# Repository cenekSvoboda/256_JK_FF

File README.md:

# 256_JK_FF
256 JK FlipFlop practical implementation

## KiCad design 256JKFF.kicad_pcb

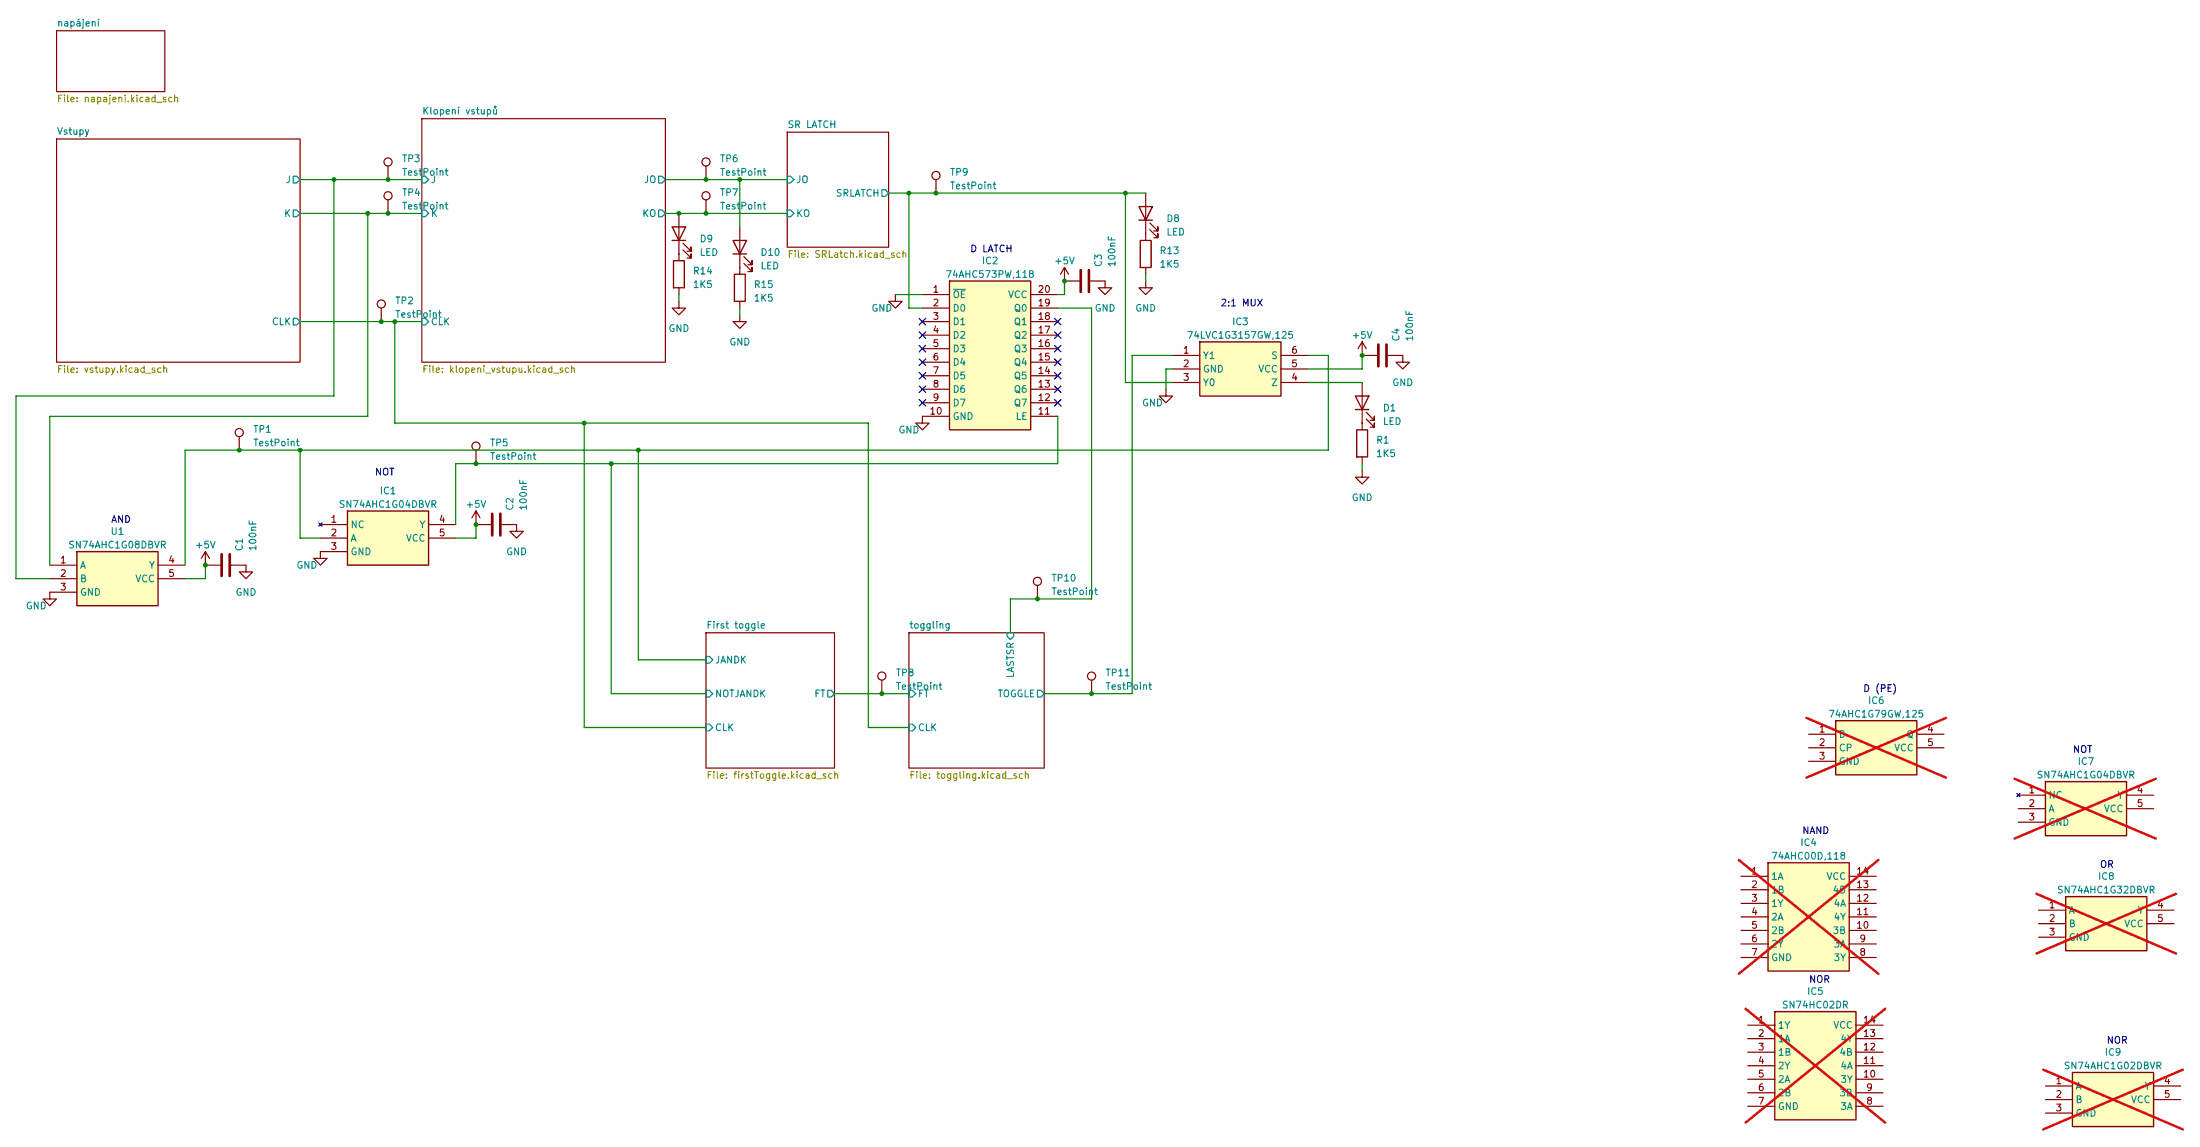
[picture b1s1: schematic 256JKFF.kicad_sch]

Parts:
C1, C2, C3, C4: 100nF; C_1206_3216Metric
D1: LED; LED_D3.0mm
D8, D9, D10: LED; LED_1206_3216Metric
IC1: SN74AHC1G04DBVR; SOT95P280X145-5N; Manufacturer_Part_Number SN74AHC1G04DBVR
IC2: 74AHC573PW,118; SOIC127P1032X265-20N; Manufacturer_Part_Number 74AHC573PW,118
IC3: 74LVC1G3157GW,125; 74LVC1G3157GW125; Manufacturer_Part_Number 74LVC1G3157GW,125
IC4: 74AHC00D,118; SOIC127P600X175-14N; Manufacturer_Part_Number 74AHC00D,118; not fitted
IC5: SN74HC02DR; SOIC127P600X175-14N; Manufacturer_Part_Number SN74HC02DR; not fitted
IC6: 74AHC1G79GW,125; SOT65P212X110-5N; Manufacturer_Part_Number 74AHC1G79GW,125; not fitted
IC7: SN74AHC1G04DBVR; SOT95P280X145-5N; Manufacturer_Part_Number SN74AHC1G04DBVR; not fitted
IC8: SN74AHC1G32DBVR; SOT95P280X145-5N; Manufacturer_Part_Number SN74AHC1G32DBVR; not fitted
IC9: SN74AHC1G02DBVR; SOT95P280X145-5N; Manufacturer_Part_Number SN74AHC1G02DBVR; not fitted
R1, R13, R14, R15: 1K5; R_1206_3216Metric
TP1, TP2, TP3, TP4, TP5, TP6, TP7, TP8, TP9, TP10, TP11: TestPoint; TestPoint_Pad_1.5x1.5mm
U1: SN74AHC1G08DBVR; SOT95P280X145-5N; Manufacturer_Part_Number SN74AHC1G08DBVR

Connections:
+5V: C1.2, C2.2, C3.2, C4.2, IC1.5 (VCC), IC2.20 (VCC), IC3.5 (VCC), U1.5 (VCC); also elsewhere on the board
/First toggle/CLK: TP2.1; also elsewhere on the board
/First toggle/FT: TP8.1; also elsewhere on the board
/First toggle/JANDK: IC1.2 (A), IC3.6 (S), TP1.1, U1.4 (Y); also elsewhere on the board
/First toggle/NOTJANDK: IC1.4 (Y), IC2.11 (LE), TP5.1; also elsewhere on the board
/Klopení vstupů/J: TP3.1, U1.2 (B); also elsewhere on the board
/Klopení vstupů/JO: D10.2 (A), TP6.1; also elsewhere on the board
/Klopení vstupů/K: TP4.1, U1.1 (A); also elsewhere on the board
/Klopení vstupů/KO: D9.2 (A), TP7.1; also elsewhere on the board
/SR LATCH/SRLATCH: D8.2 (A), IC2.2 (D0), IC3.3 (Y0), TP9.1; also elsewhere on the board
/toggling/LASTSR: IC2.19 (Q0), TP10.1; also elsewhere on the board
/toggling/TOGGLE: IC3.1 (Y1), TP11.1; also elsewhere on the board
GND: C1.1, C2.1, C3.1, C4.1, IC1.3 (GND), IC2.1 (~OE), IC2.10 (GND), IC3.2 (GND), R1.2, R13.2, R14.2, R15.2, U1.3 (GND); also elsewhere on the board
unnamed: D1.2 (A), IC3.4 (Z)
unnamed: D1.1 (K), R1.1
unnamed: D8.1 (K), R13.1
unnamed: D9.1 (K), R14.1
unnamed: D10.1 (K), R15.1

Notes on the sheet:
D (PE)
NAND
AND
NOT
2:1 MUX
NOR
D LATCH

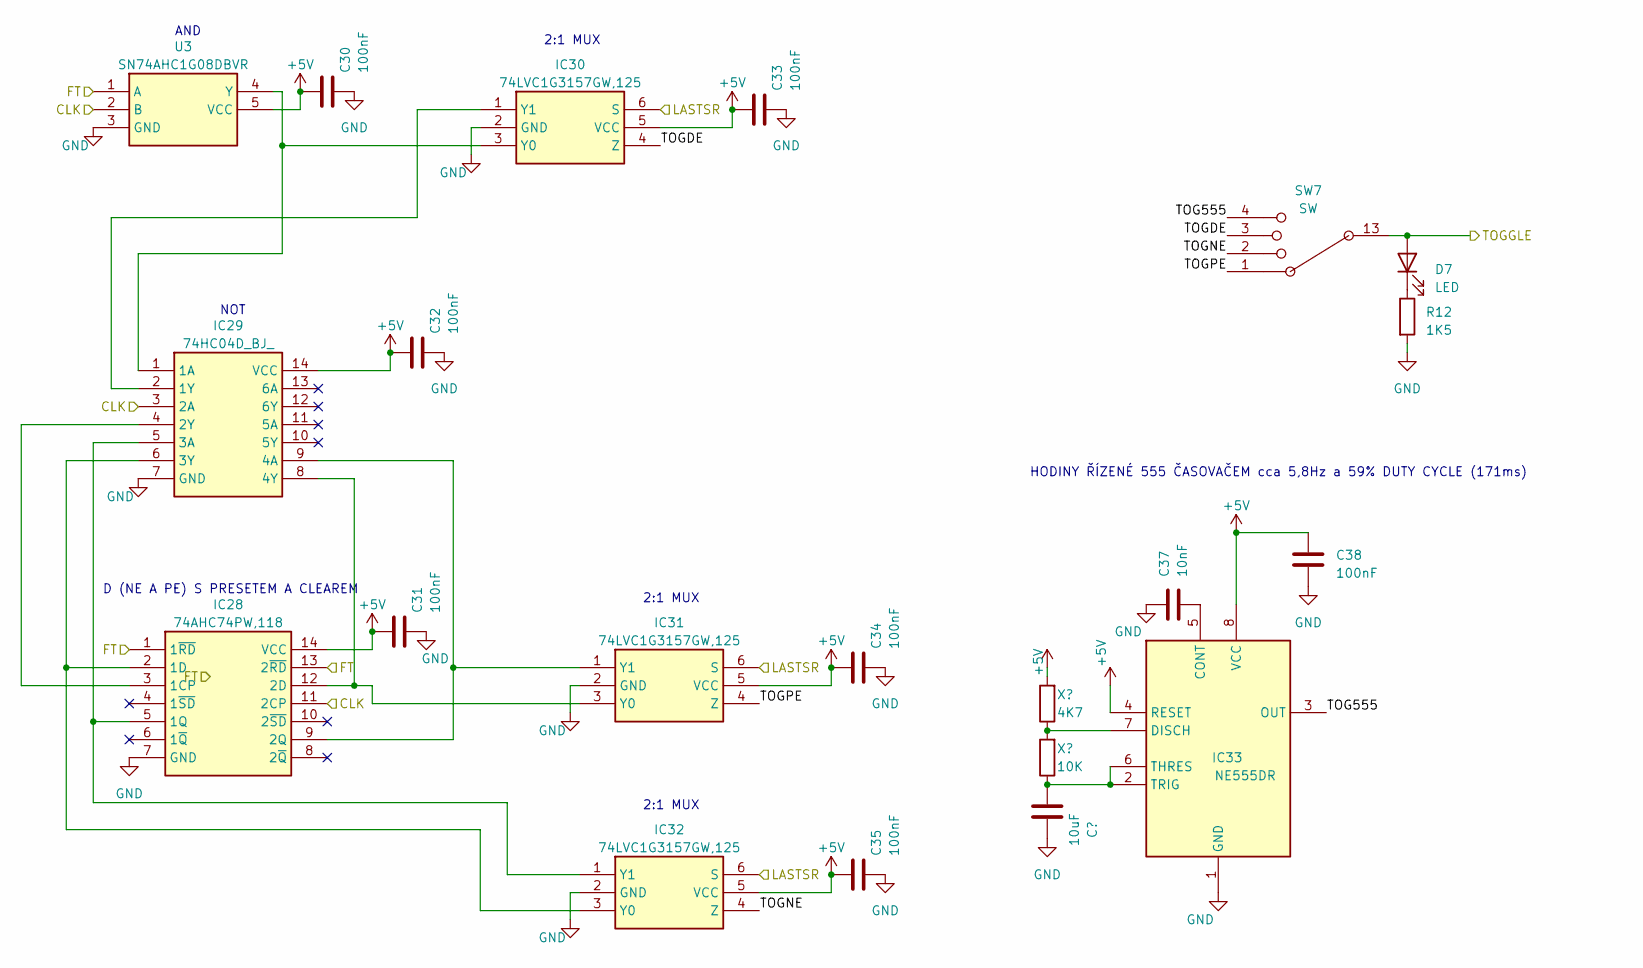
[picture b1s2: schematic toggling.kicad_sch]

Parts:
C30, C31, C32, C33, C34, C35, C38: 100nF; C_1206_3216Metric
C36: 10uF; CP_Radial_D4.0mm_P2.00mm
C37: 10nF; C_1206_3216Metric
D7: LED; LED_1206_3216Metric
IC28: 74AHC74PW,118; SOP65P640X110-14N; Manufacturer_Part_Number 74AHC74PW,118
IC29: 74HC04D_BJ_; SOIC127P600X175-14N; Manufacturer_Part_Number 74HC04D(BJ)
IC30, IC31, IC32: 74LVC1G3157GW,125; 74LVC1G3157GW125; Manufacturer_Part_Number 74LVC1G3157GW,125
IC33: NE555DR; SOIC127P600X175-8N; Manufacturer_Part_Number NE555DR
R12: 1K5; R_1206_3216Metric
SW7: SW; SLIDESWITCH ON-ON-ON-ON x
U3: SN74AHC1G08DBVR; SOT95P280X145-5N; Manufacturer_Part_Number SN74AHC1G08DBVR
X1: 4K7; R_1206_3216Metric
X2: 10K; R_1206_3216Metric

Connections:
+5V: C30.2, C31.2, C32.2, C33.2, C34.2, C35.2, C38.2, IC28.14 (VCC), IC29.14 (VCC), IC30.5 (VCC), IC31.5 (VCC), IC32.5 (VCC), IC33.4 (RESET), IC33.8 (VCC), U3.5 (VCC), X1.2; also elsewhere on the board
/First toggle/CLK: IC28.11 (2CP), IC29.3 (2A), U3.2 (B); also elsewhere on the board
/First toggle/FT: IC28.1 (1~RD), IC28.13 (2~RD), U3.1 (A); also elsewhere on the board
/toggling/LASTSR: IC30.6 (S), IC31.6 (S), IC32.6 (S); also elsewhere on the board
/toggling/TOG555: IC33.3 (OUT), SW7.4
/toggling/TOGDE: IC30.4 (Z), SW7.3
/toggling/TOGGLE: D7.2 (A), SW7.13; also elsewhere on the board
/toggling/TOGNE: IC32.4 (Z), SW7.2
/toggling/TOGPE: IC31.4 (Z), SW7.1
GND: C30.1, C31.1, C32.1, C33.1, C34.1, C35.1, C36.1, C37.1, C38.1, IC28.7 (GND), IC29.7 (GND), IC30.2 (GND), IC31.2 (GND), IC32.2 (GND), IC33.1 (GND), R12.2, U3.3 (GND); also elsewhere on the board
unnamed: D7.1 (K), R12.1
unnamed: IC28.3 (1CP), IC29.4 (2Y)
unnamed: IC28.2 (1D), IC29.6 (3Y), IC32.3 (Y0)
unnamed: IC28.5 (1Q), IC29.5 (3A), IC32.1 (Y1)
unnamed: IC28.12 (2D), IC29.8 (4Y), IC31.3 (Y0)
unnamed: IC28.9 (2Q), IC29.9 (4A), IC31.1 (Y1)
unnamed: IC29.1 (1A), IC30.3 (Y0), U3.4 (Y)
unnamed: IC29.2 (1Y), IC30.1 (Y1)
unnamed: C37.2, IC33.5 (CONT)
unnamed: IC33.7 (DISCH), X1.1, X2.2
unnamed: C36.2, IC33.2 (TRIG), IC33.6 (THRES), X2.1

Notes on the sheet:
NOT
2:1 MUX
D (NE A PE) S PRESETEM A CLEAREM
AND
HODINY ŘÍZENÉ 555 ČASOVAČEM cca 5,8Hz a 59% DUTY CYCLE (171ms)

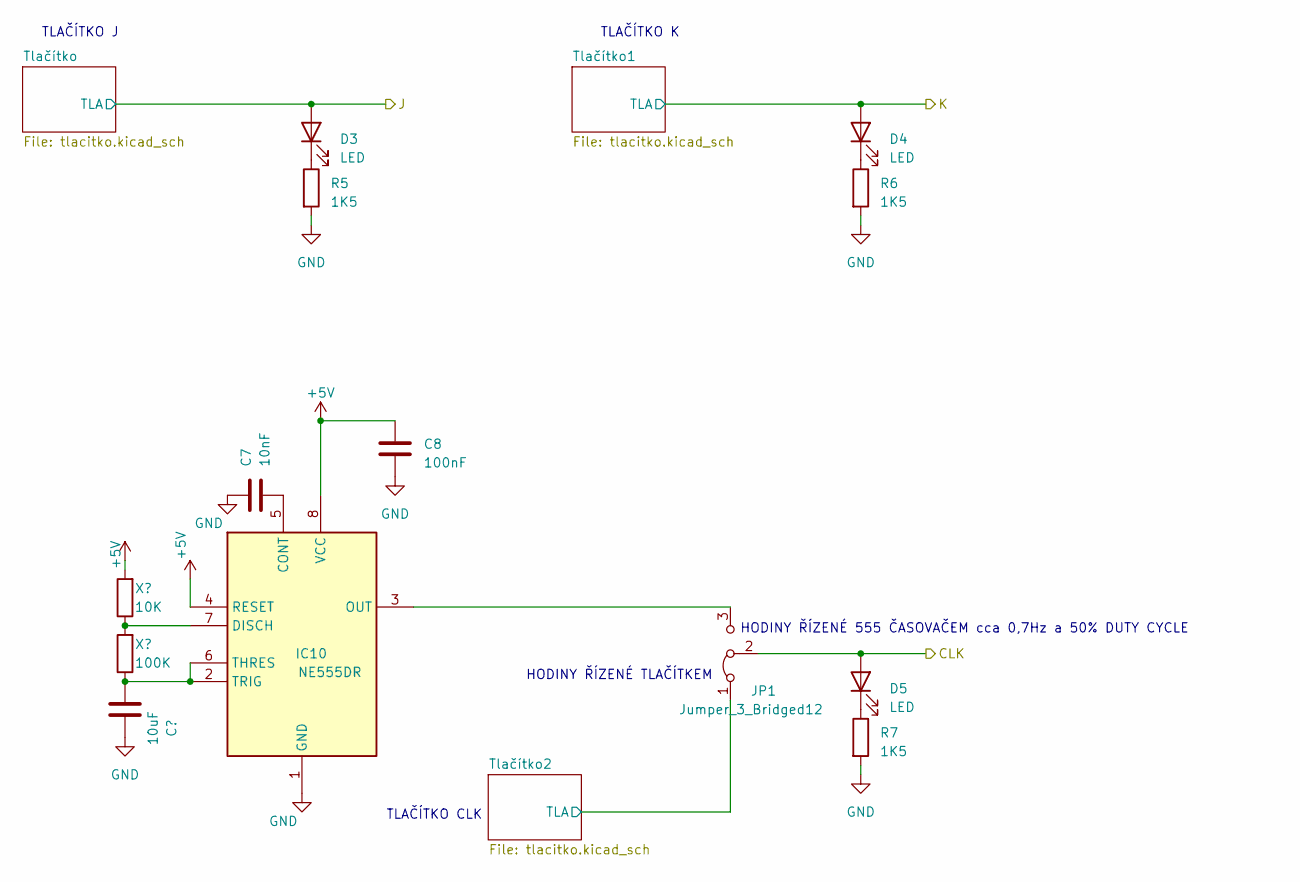
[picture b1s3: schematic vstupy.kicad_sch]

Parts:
C6: 10uF; CP_Radial_D4.0mm_P2.00mm
C7: 10nF; C_1206_3216Metric
C8: 100nF; C_1206_3216Metric
D3, D4, D5: LED; LED_1206_3216Metric
IC10: NE555DR; SOIC127P600X175-8N; Manufacturer_Part_Number NE555DR
JP1: Jumper_3_Bridged12; PinHeader_1x03_P2.54mm_Vertical
R3: 10K; R_1206_3216Metric
R4: 100K; R_1206_3216Metric
R5, R6, R7: 1K5; R_1206_3216Metric

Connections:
+5V: C8.2, IC10.4 (RESET), IC10.8 (VCC), R3.2; also elsewhere on the board
/First toggle/CLK: D5.2 (A), JP1.2 (C); also elsewhere on the board
/Klopení vstupů/J: D3.2 (A); also elsewhere on the board
/Klopení vstupů/K: D4.2 (A); also elsewhere on the board
/Vstupy/Tlačítko2/TLA: JP1.1 (A); also elsewhere on the board
GND: C6.1, C7.1, C8.1, IC10.1 (GND), R5.2, R6.2, R7.2; also elsewhere on the board
unnamed: D3.1 (K), R5.1
unnamed: D4.1 (K), R6.1
unnamed: D5.1 (K), R7.1
unnamed: C7.2, IC10.5 (CONT)
unnamed: IC10.7 (DISCH), R3.1, R4.2
unnamed: IC10.3 (OUT), JP1.3 (B)
unnamed: C6.2, IC10.2 (TRIG), IC10.6 (THRES), R4.1

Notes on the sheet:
HODINY ŘÍZENÉ 555 ČASOVAČEM cca 0,7Hz a 50% DUTY CYCLE
TLAČÍTKO K
HODINY ŘÍZENÉ TLAČÍTKEM
TLAČÍTKO J
TLAČÍTKO CLK

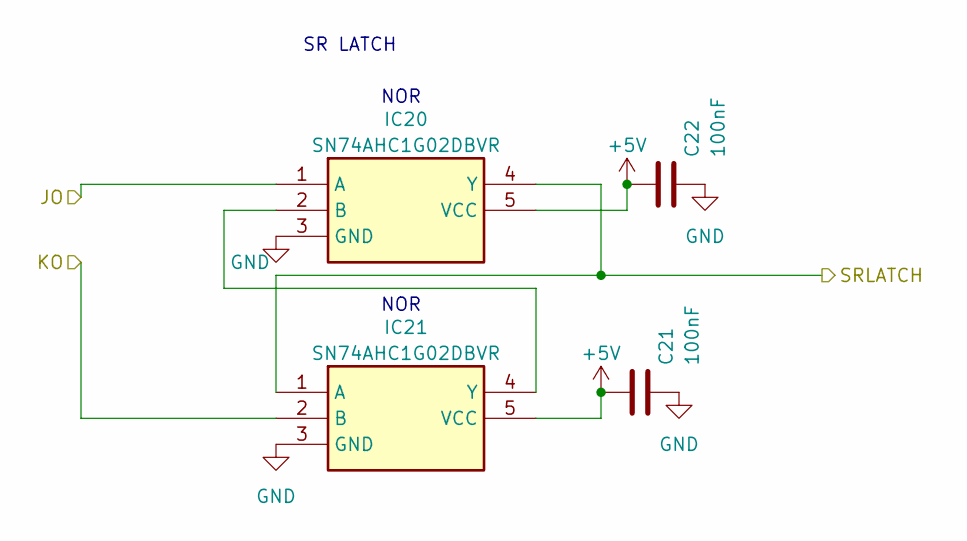
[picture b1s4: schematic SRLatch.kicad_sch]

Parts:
C21, C22: 100nF; C_1206_3216Metric
IC20, IC21: SN74AHC1G02DBVR; SOT95P280X145-5N; Manufacturer_Part_Number SN74AHC1G02DBVR

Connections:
+5V: C21.2, C22.2, IC20.5 (VCC), IC21.5 (VCC); also elsewhere on the board
/Klopení vstupů/JO: IC20.1 (A); also elsewhere on the board
/Klopení vstupů/KO: IC21.2 (B); also elsewhere on the board
/SR LATCH/SRLATCH: IC20.4 (Y), IC21.1 (A); also elsewhere on the board
GND: C21.1, C22.1, IC20.3 (GND), IC21.3 (GND); also elsewhere on the board
unnamed: IC20.2 (B), IC21.4 (Y)

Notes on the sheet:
NOR
SR LATCH

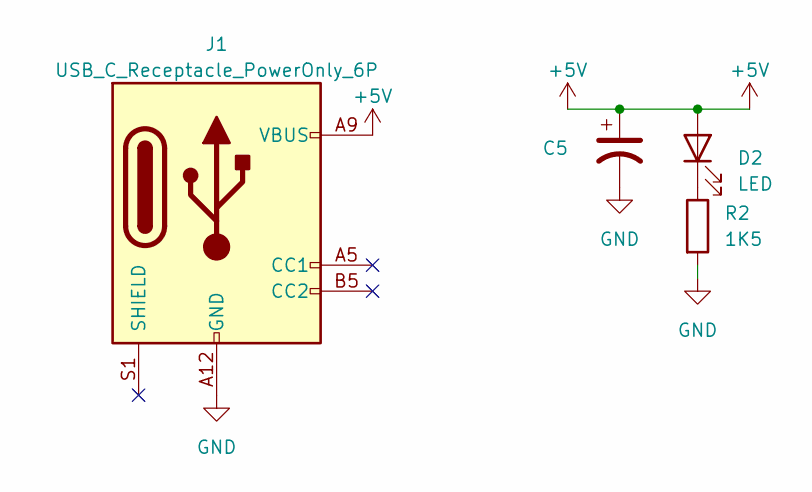
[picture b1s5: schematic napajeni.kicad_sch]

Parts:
C5: 293D106X96R3A2TE3; CAPMP3216X180N
D2: LED; LED_1206_3216Metric
J1: USB_C_Receptacle_PowerOnly_6P; GCT_USB4125-GF-A_REVA2 USB C FEMALE
R2: 1K5; R_1206_3216Metric

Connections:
+5V: C5.1, D2.2 (A), J1.A9 (VBUS), J1.B9 (VBUS); also elsewhere on the board
GND: C5.2, J1.A12 (GND), J1.B12 (GND), R2.2; also elsewhere on the board
unnamed: D2.1 (K), R2.1

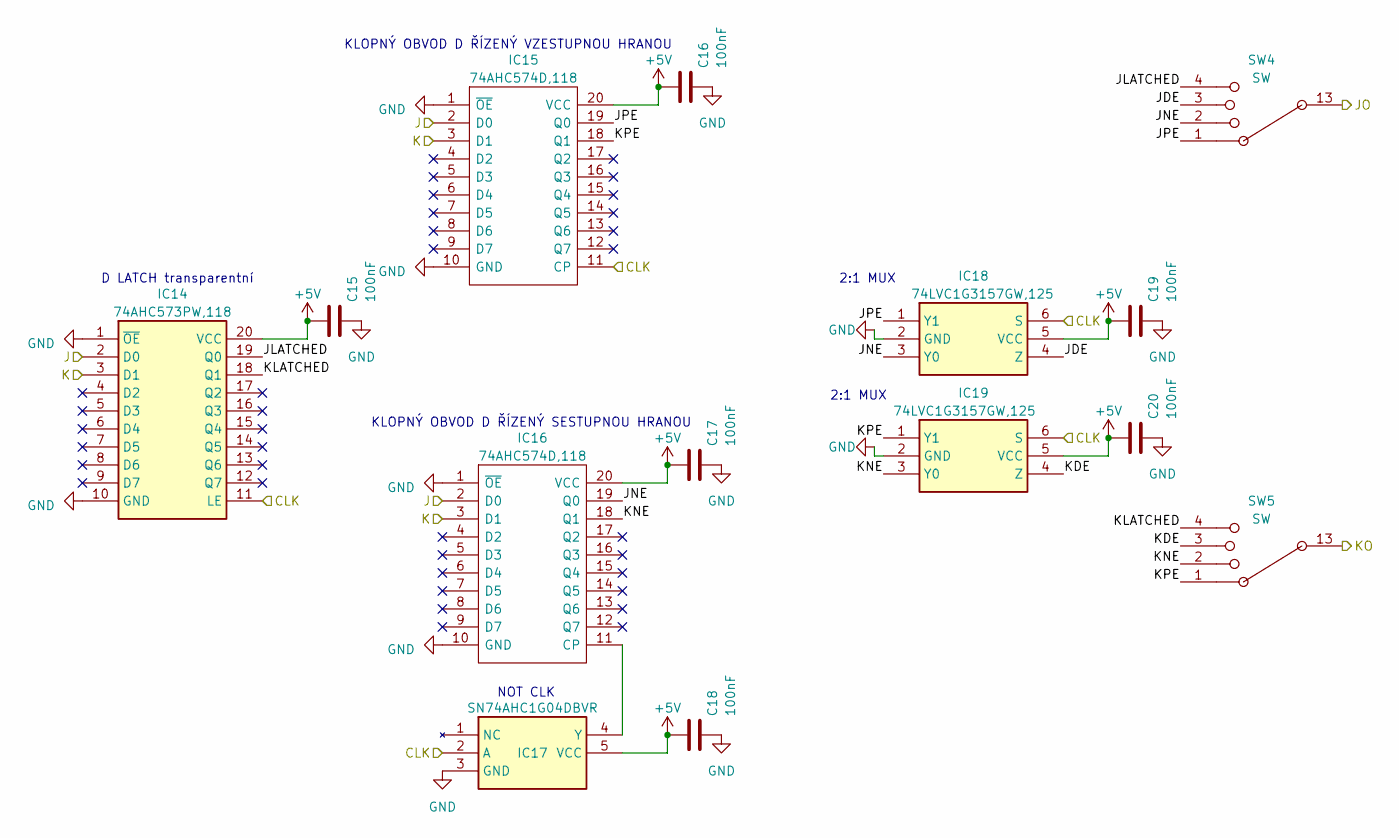
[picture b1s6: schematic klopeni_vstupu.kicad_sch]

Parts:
C15, C16, C17, C18, C19, C20: 100nF; C_1206_3216Metric
IC14: 74AHC573PW,118; SOIC127P1032X265-20N; Manufacturer_Part_Number 74AHC573PW,118
IC15, IC16: 74AHC574D,118; SOIC127P1032X265-20N; Manufacturer_Part_Number 74AHC574D,118
IC17: SN74AHC1G04DBVR; SOT95P280X145-5N; Manufacturer_Part_Number SN74AHC1G04DBVR
IC18, IC19: 74LVC1G3157GW,125; 74LVC1G3157GW125; Manufacturer_Part_Number 74LVC1G3157GW,125
SW4, SW5: SW; SLIDESWITCH ON-ON-ON-ON x

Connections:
+5V: C15.2, C16.2, C17.2, C18.2, C19.2, C20.2, IC14.20 (VCC), IC15.20 (VCC), IC16.20 (VCC), IC17.5 (VCC), IC18.5 (VCC), IC19.5 (VCC); also elsewhere on the board
/First toggle/CLK: IC14.11 (LE), IC15.11 (CP), IC17.2 (A), IC18.6 (S), IC19.6 (S); also elsewhere on the board
/Klopení vstupů/J: IC14.2 (D0), IC15.2 (D0), IC16.2 (D0); also elsewhere on the board
/Klopení vstupů/JDE: IC18.4 (Z), SW4.3
/Klopení vstupů/JLATCHED: IC14.19 (Q0), SW4.4
/Klopení vstupů/JNE: IC16.19 (Q0), IC18.3 (Y0), SW4.2
/Klopení vstupů/JO: SW4.13; also elsewhere on the board
/Klopení vstupů/JPE: IC15.19 (Q0), IC18.1 (Y1), SW4.1
/Klopení vstupů/K: IC14.3 (D1), IC15.3 (D1), IC16.3 (D1); also elsewhere on the board
/Klopení vstupů/KDE: IC19.4 (Z), SW5.3
/Klopení vstupů/KLATCHED: IC14.18 (Q1), SW5.4
/Klopení vstupů/KNE: IC16.18 (Q1), IC19.3 (Y0), SW5.2
/Klopení vstupů/KO: SW5.13; also elsewhere on the board
/Klopení vstupů/KPE: IC15.18 (Q1), IC19.1 (Y1), SW5.1
GND: C15.1, C16.1, C17.1, C18.1, C19.1, C20.1, IC14.1 (~OE), IC14.10 (GND), IC15.1 (~OE), IC15.10 (GND), IC16.1 (~OE), IC16.10 (GND), IC17.3 (GND), IC18.2 (GND), IC19.2 (GND); also elsewhere on the board
unnamed: IC16.11 (CP), IC17.4 (Y)

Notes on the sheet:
KLOPNÝ OBVOD D ŘÍZENÝ VZESTUPNOU HRANOU
2:1 MUX
KLOPNÝ OBVOD D ŘÍZENÝ SESTUPNOU HRANOU
NOT CLK
D LATCH transparentní

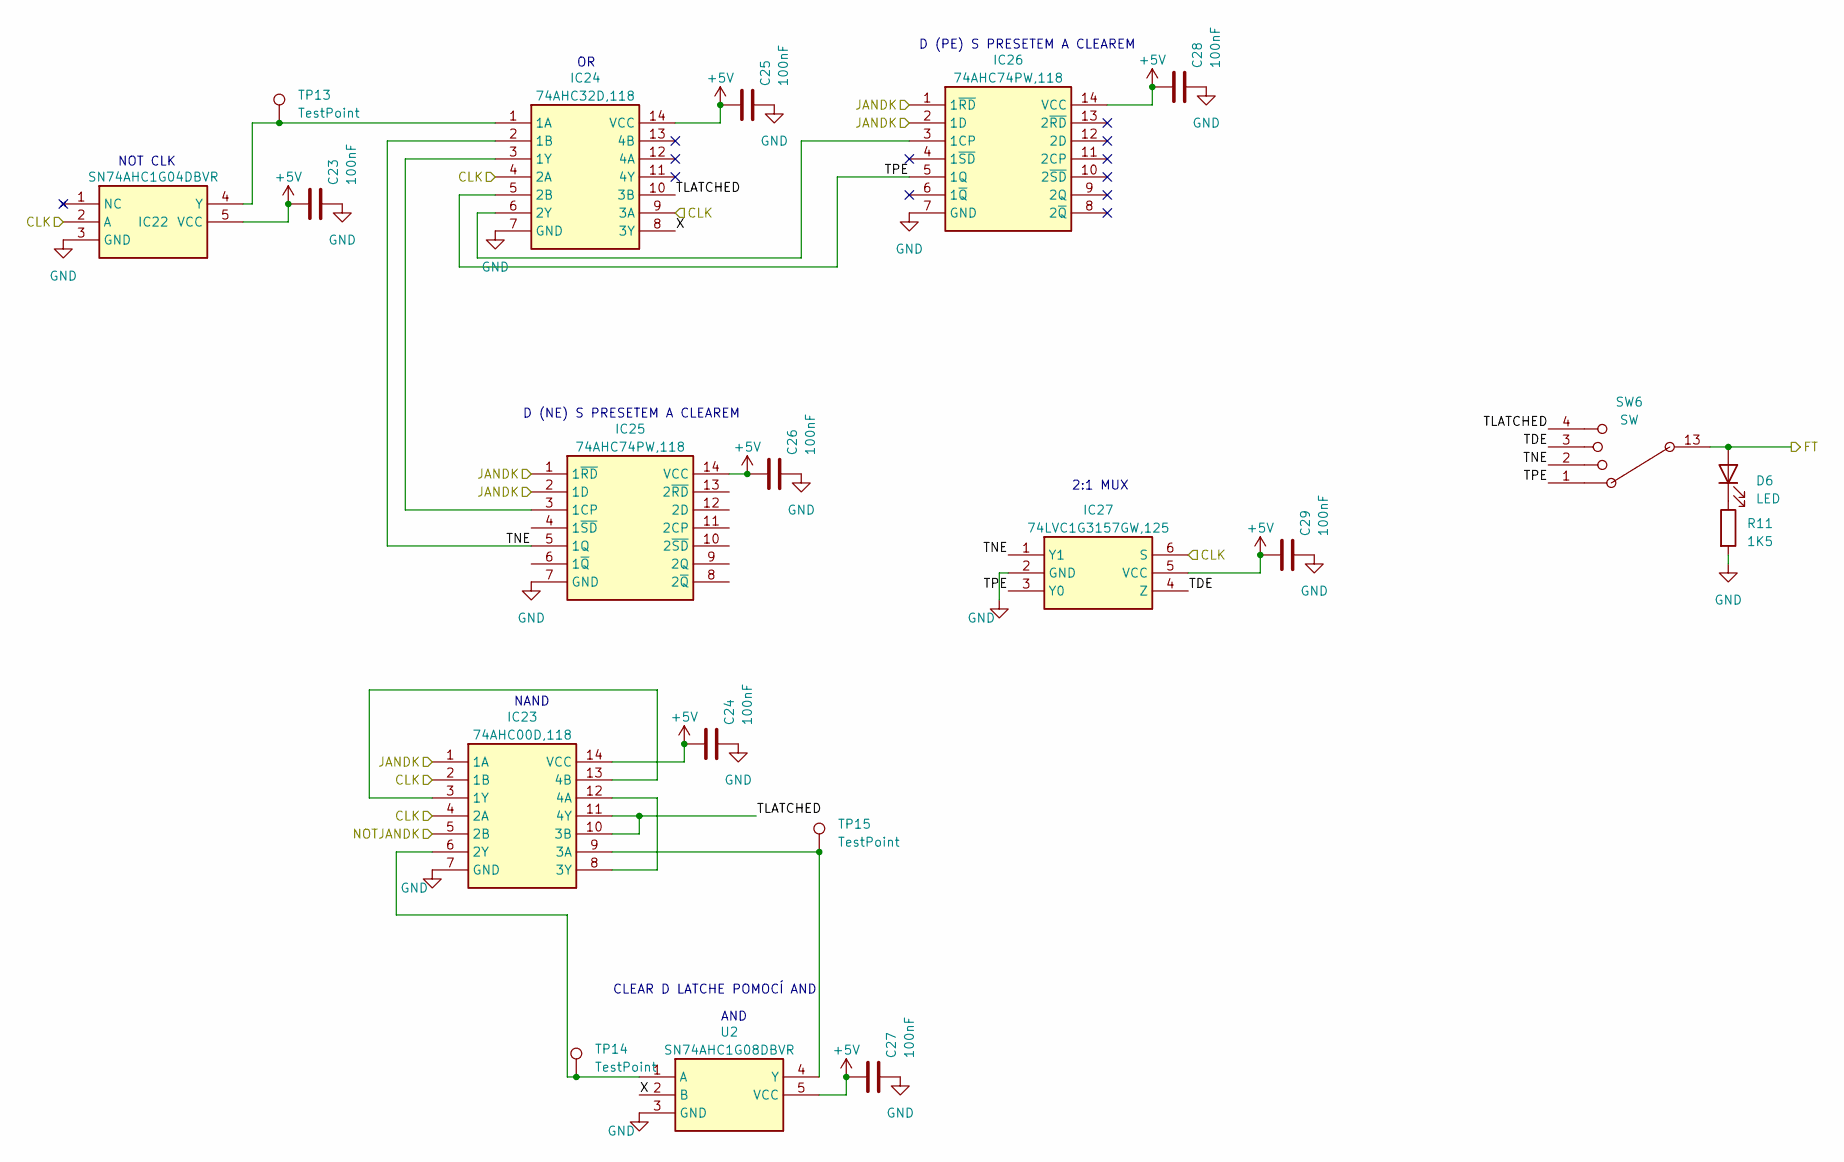
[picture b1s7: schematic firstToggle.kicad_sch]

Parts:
C23, C24, C25, C26, C27, C28, C29: 100nF; C_1206_3216Metric
D6: LED; LED_1206_3216Metric
IC22: SN74AHC1G04DBVR; SOT95P280X145-5N; Manufacturer_Part_Number SN74AHC1G04DBVR
IC23: 74AHC00D,118; SOIC127P600X175-14N; Manufacturer_Part_Number 74AHC00D,118
IC24: 74AHC32D,118; SOIC127P600X175-14N; Manufacturer_Part_Number 74AHC32D,118
IC25, IC26: 74AHC74PW,118; SOP65P640X110-14N; Manufacturer_Part_Number 74AHC74PW,118
IC27: 74LVC1G3157GW,125; 74LVC1G3157GW125; Manufacturer_Part_Number 74LVC1G3157GW,125
R11: 1K5; R_1206_3216Metric
SW6: SW; SLIDESWITCH ON-ON-ON-ON x
TP13, TP14, TP15: TestPoint; TestPoint_Pad_1.5x1.5mm
U2: SN74AHC1G08DBVR; SOT95P280X145-5N; Manufacturer_Part_Number SN74AHC1G08DBVR

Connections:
+5V: C23.2, C24.2, C25.2, C26.2, C27.2, C28.2, C29.2, IC22.5 (VCC), IC23.14 (VCC), IC24.14 (VCC), IC25.14 (VCC), IC26.14 (VCC), IC27.5 (VCC), U2.5 (VCC); also elsewhere on the board
/First toggle/CLK: IC22.2 (A), IC23.2 (1B), IC23.4 (2A), IC24.4 (2A), IC24.9 (3A), IC27.6 (S); also elsewhere on the board
/First toggle/FT: D6.2 (A), SW6.13; also elsewhere on the board
/First toggle/JANDK: IC23.1 (1A), IC25.1 (1~RD), IC25.2 (1D), IC26.1 (1~RD), IC26.2 (1D); also elsewhere on the board
/First toggle/NOTJANDK: IC23.5 (2B); also elsewhere on the board
/First toggle/TDE: IC27.4 (Z), SW6.3
/First toggle/TLATCHED: IC23.10 (3B), IC23.11 (4Y), IC24.10 (3B), SW6.4
/First toggle/TNE: IC24.2 (1B), IC25.5 (1Q), IC27.1 (Y1), SW6.2
/First toggle/TPE: IC24.5 (2B), IC26.5 (1Q), IC27.3 (Y0), SW6.1
/First toggle/X: IC24.8 (3Y), U2.2 (B)
GND: C23.1, C24.1, C25.1, C26.1, C27.1, C28.1, C29.1, IC22.3 (GND), IC23.7 (GND), IC24.7 (GND), IC25.7 (GND), IC26.7 (GND), IC27.2 (GND), R11.2, U2.3 (GND); also elsewhere on the board
unnamed: D6.1 (K), R11.1
unnamed: IC22.4 (Y), IC24.1 (1A), TP13.1
unnamed: IC23.3 (1Y), IC23.13 (4B)
unnamed: IC23.6 (2Y), TP14.1, U2.1 (A)
unnamed: IC23.9 (3A), TP15.1, U2.4 (Y)
unnamed: IC23.8 (3Y), IC23.12 (4A)
unnamed: IC24.3 (1Y), IC25.3 (1CP)
unnamed: IC24.6 (2Y), IC26.3 (1CP)

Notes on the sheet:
NAND
D (PE) S PRESETEM A CLEAREM
D (NE) S PRESETEM A CLEAREM
AND
2:1 MUX
CLEAR D LATCHE POMOCÍ AND
NOT CLK

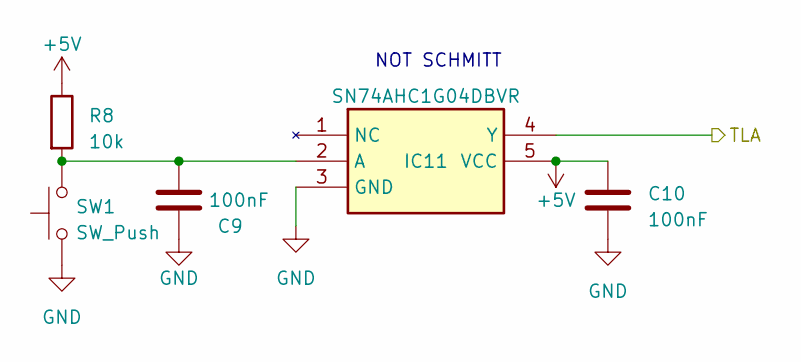
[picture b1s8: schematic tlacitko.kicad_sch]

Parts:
C9, C10: 100nF; C_1206_3216Metric
IC11: SN74AHC1G04DBVR; SOT95P280X145-5N; Manufacturer_Part_Number SN74AHC1G04DBVR
R8: 10k; R_1206_3216Metric
SW1: SW_Push; SW_PUSH_6mm_H7.3mm

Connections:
+5V: C10.2, IC11.5 (VCC), R8.1; also elsewhere on the board
/Klopení vstupů/J: IC11.4 (Y); also elsewhere on the board
GND: C9.1, C10.1, IC11.3 (GND), SW1.1; also elsewhere on the board
unnamed: C9.2, IC11.2 (A), R8.2, SW1.2

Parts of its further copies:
C11, C12, C13, C14: 100nF; C_1206_3216Metric
IC12, IC13: SN74AHC1G04DBVR; SOT95P280X145-5N; Manufacturer_Part_Number SN74AHC1G04DBVR
R9, R10: 10k; R_1206_3216Metric
SW2, SW3: SW_Push; SW_PUSH_6mm_H7.3mm

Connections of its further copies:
+5V: C12.2, C14.2, IC12.5 (VCC), IC13.5 (VCC), R9.1, R10.1; also elsewhere on the board
/Klopení vstupů/K: IC12.4 (Y); also elsewhere on the board
/Vstupy/Tlačítko2/TLA: IC13.4 (Y); also elsewhere on the board
GND: C11.1, C12.1, C13.1, C14.1, IC12.3 (GND), IC13.3 (GND), SW2.1, SW3.1; also elsewhere on the board
unnamed: C11.2, IC12.2 (A), R9.2, SW2.2
unnamed: C13.2, IC13.2 (A), R10.2, SW3.2

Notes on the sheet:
NOT SCHMITT

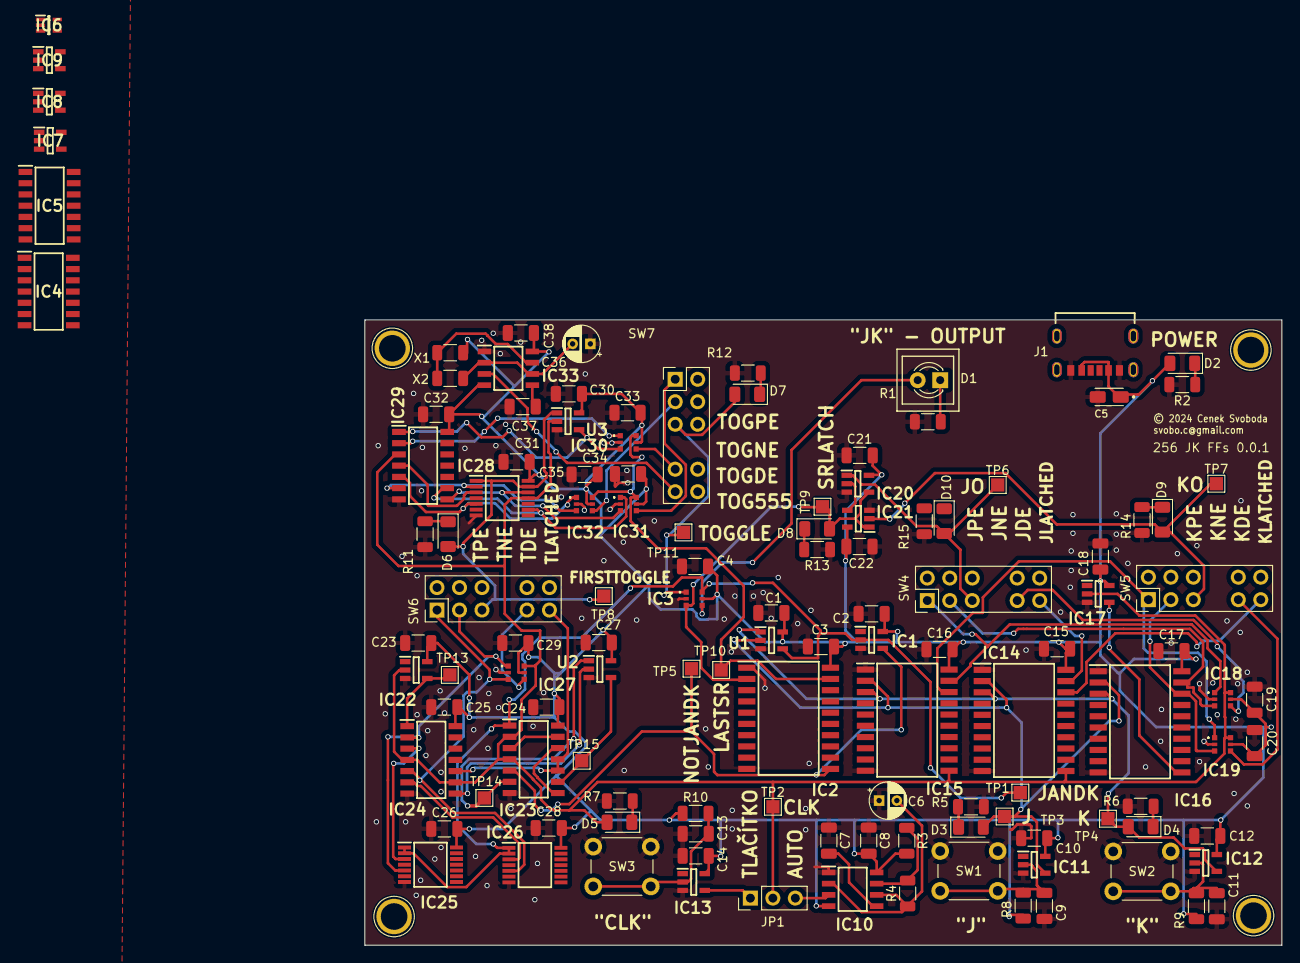
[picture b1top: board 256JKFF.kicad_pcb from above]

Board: 2 copper layers, 103.6 x 70.6 mm, 124 parts (0 on the bottom side), 68 nets.

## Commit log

2024-04-04 initial (and last) commit

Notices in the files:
256JKFF.kicad_pcb:
© 2024 Cenek Svoboda
